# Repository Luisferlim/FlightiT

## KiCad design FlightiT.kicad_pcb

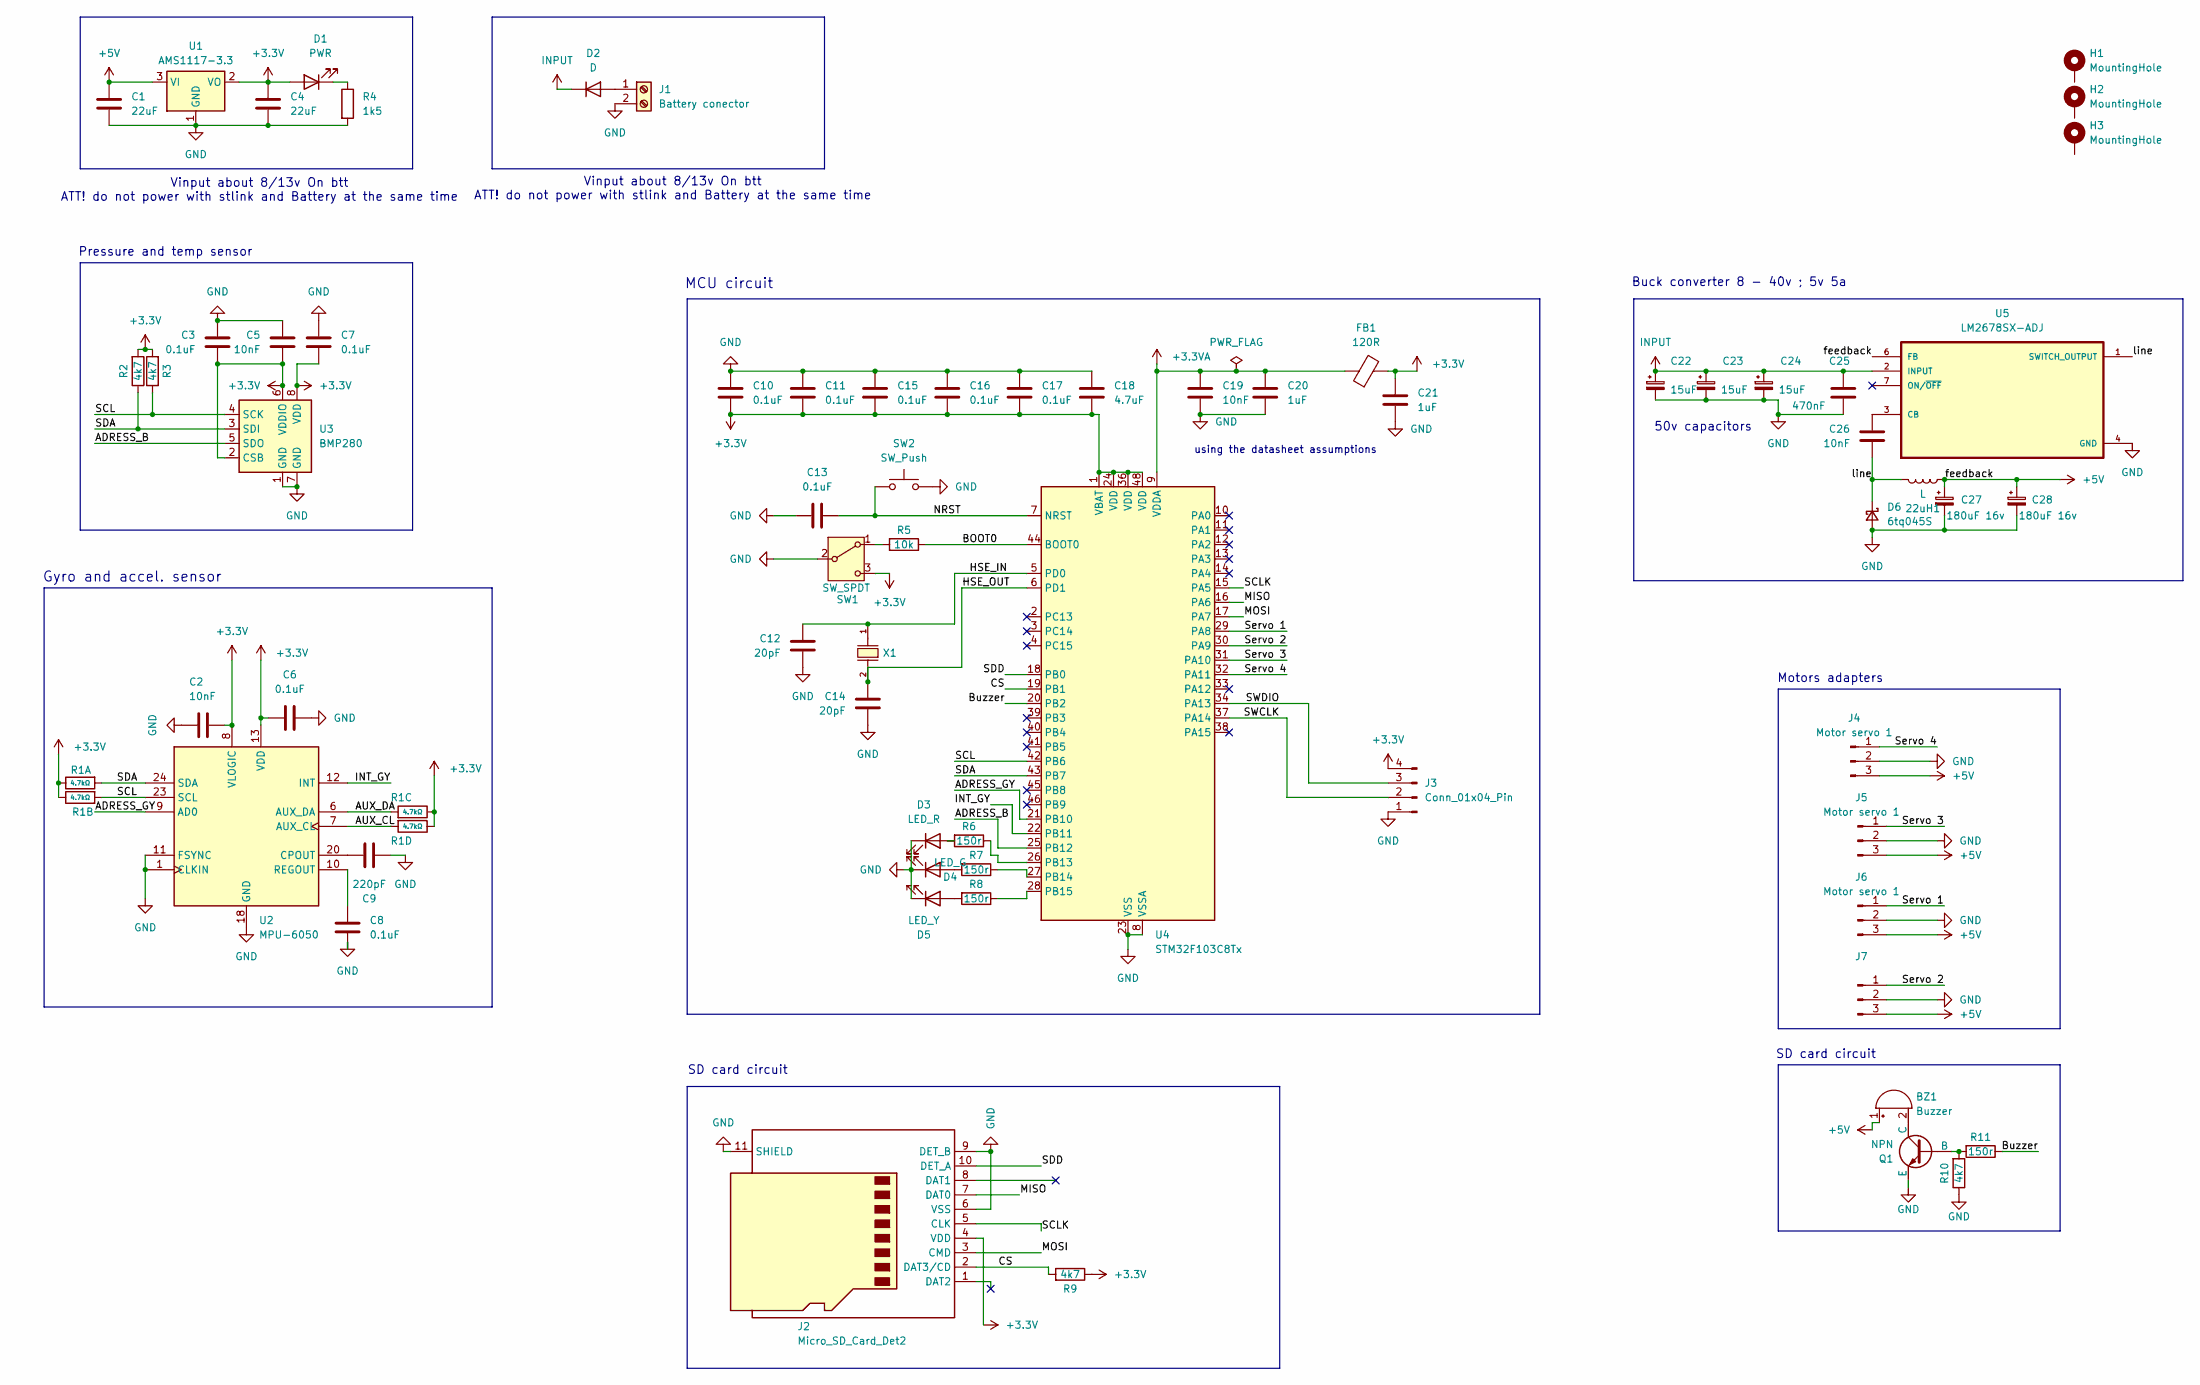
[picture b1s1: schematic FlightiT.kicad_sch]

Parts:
22uH1: L; L_Changjiang_FXL1040
BZ1: Buzzer; Buzzer_12x9.5RM7.6
C1, C4: 22uF; C_1206_3216Metric
C2, C5, C19, C26: 10nF; C_0805_2012Metric
C3, C6, C7, C8, C10, C11, C13, C15, C16, C17: 0.1uF; C_0402_1005Metric
C9: 220pF; C_0402_1005Metric
C12, C14: 20pF; C_0402_1005Metric
C18: 4.7uF; C_0805_2012Metric
C20, C21: 1uF; C_1206_3216Metric
C22, C23, C24: 15uF; CP_Radial_D5.0mm_P2.50mm
C25: 470nF; C_0402_1005Metric
C27, C28: 180uF 16v; CP_Radial_D5.0mm_P2.50mm
D1: PWR; LED_0603_1608Metric
D2: D; D_SOD-323
D3: LED_R; LED_0603_1608Metric
D4: LED_G; LED_0603_1608Metric
D5: LED_Y; LED_0603_1608Metric
D6: 6tq045S; TO-263-2_TabPin1
FB1: 120R; L_0603_1608Metric
H1, H2, H3: MountingHole; MountingHole_3.2mm_M3_ISO7380_Pad
J1: Battery conector; TerminalBlock_MaiXu_MX126-5.0-02P_1x02_P5.00mm
J2: Micro_SD_Card_Det2; microSD_HC_Molex_47219-2001
J3: Conn_01x04_Pin; PinHeader_1x04_P2.54mm_Horizontal
J4, J5, J6: Motor servo 1; PinHeader_1x03_P2.54mm_Vertical
J7: Motor servo 2; PinHeader_1x03_P2.54mm_Vertical
Q1: NPN; SOT-23
R1: 4.7kΩ; R_Array_Concave_4x0603; Tolerance ±5%; Part 4D03WGJ0472T5E; LCSC C1980
R2, R3, R9, R10: 4k7; R_0603_1608Metric
R4: 1k5; R_0603_1608Metric
R5: 10k; R_0603_1608Metric
R6, R7, R8, R11: 150r; R_0603_1608Metric
SW1: SW_SPDT; SW_SPDT_PCM12
SW2: SW_Push; SW_TS-1088-AR02016
U1: AMS1117-3.3; SOT-223-3_TabPin2
U2: MPU-6050; InvenSense_QFN-24_4x4mm_P0.5mm
U3: BMP280; Bosch_LGA-8_2x2.5mm_P0.65mm_ClockwisePinNumbering
U4: STM32F103C8Tx; LQFP-48_7x7mm_P0.5mm
U5: LM2678SX-ADJ; TO127P1435X464-8N
X1: X50328MSB2GI; Crystal_SMD_5032-2Pin_5.0x3.2mm; Frequency Tolerance ±10ppm; Part X50328MSB2GI; LCSC C115962

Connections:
+3.3V: C2.1, C3.2, C4.2, C5.2, C6.2, C7.2, C10.1, C11.1, C15.1, C16.1, C17.1, C18.1, C21.2, D1.2 (A), FB1.2, J2.4 (VDD), J3.4, R1.5, R1.6, R1.7, R1.8, R2.2, R3.2, R9.1, SW1.3 (C), U1.2 (VO), U2.8 (VLOGIC), U2.13 (VDD), U3.2 (CSB), U3.6 (VDDIO), U3.8 (VDD), U4.1 (VBAT), U4.24 (VDD), U4.36 (VDD), U4.48 (VDD); also elsewhere on the board
+3.3VA: C19.2, C20.2, FB1.1, U4.9 (VDDA)
+5V: 22uH1.1, BZ1.1 (+), C1.2, C27.1, C28.1, J4.3, J5.3, J6.3, J7.3, U1.3 (VI), U5.6 (FB); also elsewhere on the board
/ADRESS_B: U3.5 (SDO), U4.25 (PB12)
/ADRESS_GY: U2.9 (AD0), U4.21 (PB10)
/AUX_CL: R1.4, U2.7 (AUX_CL)
/AUX_DA: R1.3, U2.6 (AUX_DA)
/BOOT0: R5.1, U4.44 (BOOT0)
/Buzzer: R11.1, U4.20 (PB2)
/CS: J2.2 (DAT3/CD), R9.2, U4.19 (PB1)
/HSE_IN: C12.1, U4.5 (PD0), X1.1
/HSE_OUT: C14.2, U4.6 (PD1), X1.2
/INT_GY: U2.12 (INT), U4.22 (PB11)
/MISO: J2.7 (DAT0), U4.16 (PA6)
/MOSI: J2.3 (CMD), U4.17 (PA7)
/NRST: C13.1, SW2.1, U4.7 (NRST)
/SCL: R1.2, R3.1, U2.23 (SCL), U3.4 (SCK), U4.42 (PB6)
/SCLK: J2.5 (CLK), U4.15 (PA5)
/SDA: R1.1, R2.1, U2.24 (SDA), U3.3 (SDI), U4.43 (PB7); also elsewhere on the board
/SDD: J2.10 (DET_A), U4.18 (PB0)
/SWCLK: J3.2, U4.37 (PA14)
/SWDIO: J3.3, U4.34 (PA13)
/Servo 1: J6.1, U4.29 (PA8)
/Servo 2: J7.1, U4.30 (PA9)
/Servo 3: J5.1, U4.31 (PA10)
/Servo 4: J4.1, U4.32 (PA11)
/line: 22uH1.2, C26.1, D6.1 (K), U5.1 (SWITCH_OUTPUT); also elsewhere on the board
GND: C1.1, C2.2, C3.1, C4.1, C5.1, C6.1, C7.1, C8.1, C9.1, C10.2, C11.2, C12.2, C13.2, C14.1, C15.2, C16.2, C17.2, C18.2, C19.1, C20.1, C21.1, C22.2, C23.2, C24.2, C25.2, C27.2, C28.2, D3.1 (K), D4.1 (K), D5.1 (K), D6.2 (A), J1.2, J2.6 (VSS), J2.9 (DET_B), J2.11 (SHIELD), J3.1, J4.2, J5.2, J6.2, J7.2, Q1.3 (E), R4.2, R10.1, SW1.2 (B), SW2.2, U1.1 (GND), U2.1 (CLKIN), U2.11 (FSYNC), U2.18 (GND), U3.1 (GND), U3.7 (GND), U4.8 (VSSA), U4.23 (VSS), U4.35 (VSS), U4.47 (VSS), U5.4 (GND)
INPUT: C22.1, C23.1, C24.1, C25.1, D2.1 (K), U5.2 (INPUT)
unnamed: BZ1.2 (-), Q1.1 (C)
unnamed: D1.1 (K), R4.1
unnamed: D2.2 (A), J1.1
unnamed: D3.2 (A), R6.2
unnamed: D4.2 (A), R7.2
unnamed: D5.2 (A), R8.2
unnamed: Q1.2 (B), R10.2, R11.2
unnamed: R5.2, SW1.1 (A)
unnamed: C9.2, U2.20 (CPOUT)
unnamed: C8.2, U2.10 (REGOUT)
unnamed: R6.1, U4.26 (PB13)
unnamed: R7.1, U4.27 (PB14)
unnamed: R8.1, U4.28 (PB15)
unnamed: C26.2, U5.3 (CB)

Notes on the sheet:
Vinput about 8/13v On btt ATT! do not power with stlink and Battery at the same time
Buck converter 8 - 40v ; 5v 5a
Pressure and temp sensor
MCU circuit
50v capacitors
Motors adapters
SD card circuit
Gyro and accel. sensor
using the datasheet assumptions

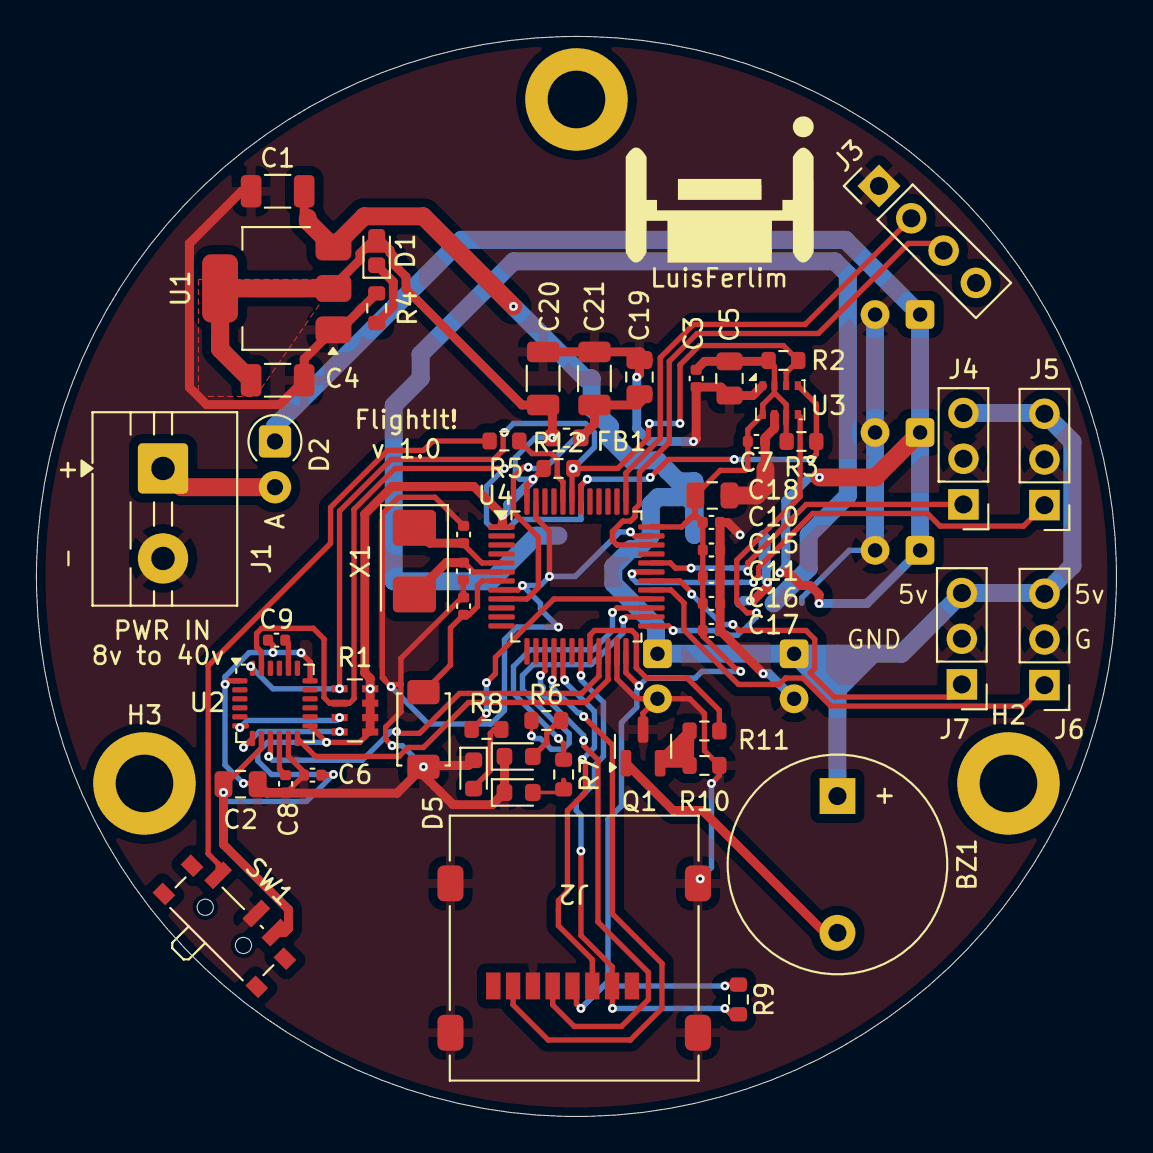
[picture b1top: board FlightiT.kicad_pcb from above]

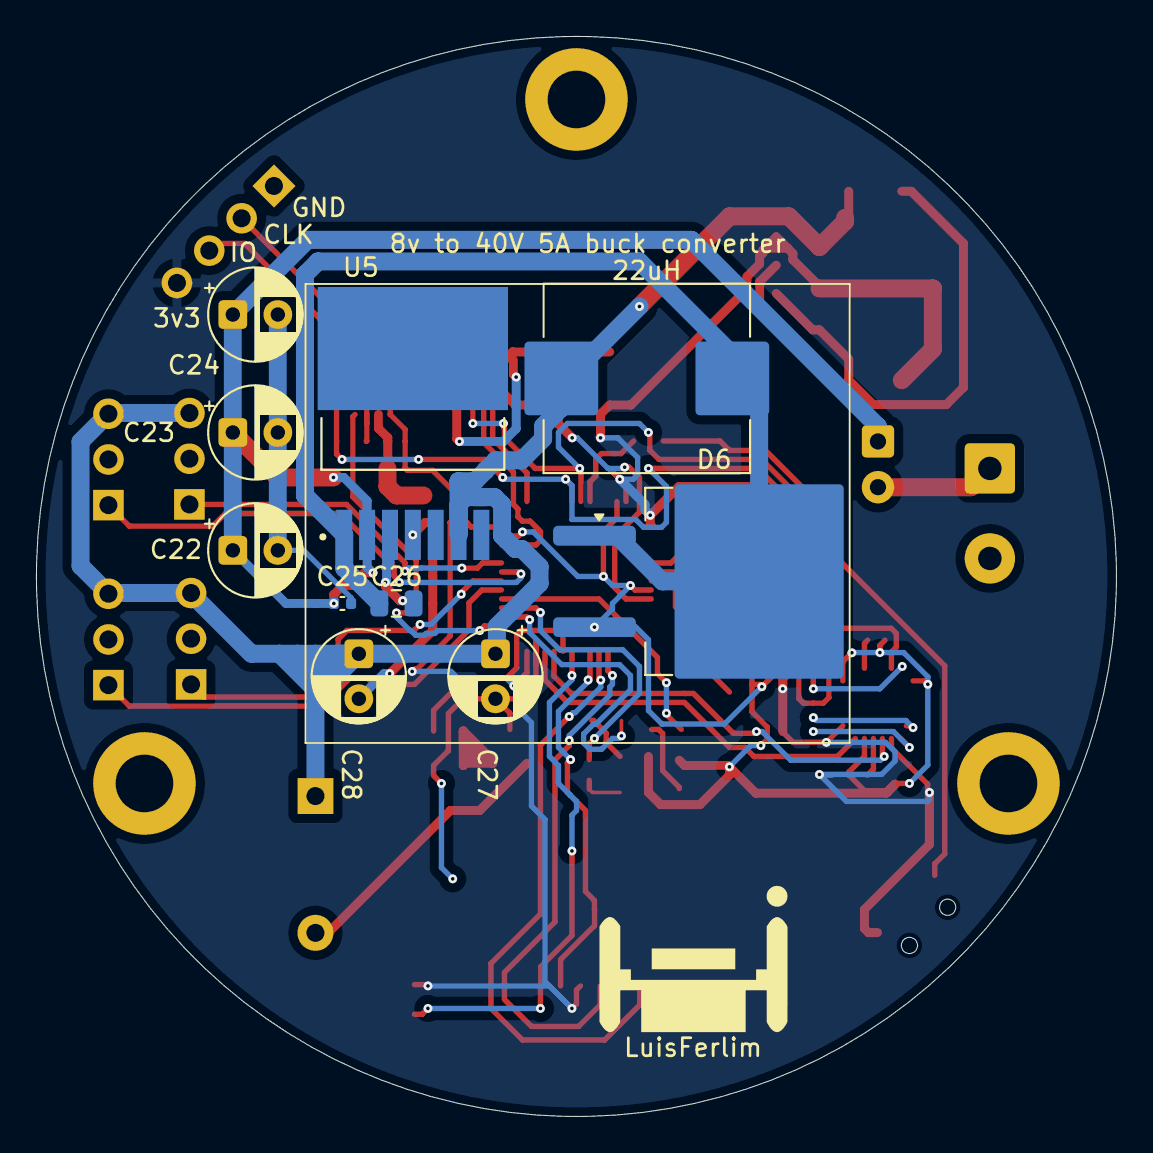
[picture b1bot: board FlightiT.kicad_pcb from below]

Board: 2 copper layers, 60.0 x 60.0 mm, 68 parts (10 on the bottom side), 42 nets.

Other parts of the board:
22uH: L; L_Changjiang_FXL1040
R12: 1k5; R_0603_1608Metric

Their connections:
+3.3V: R12.1; also elsewhere on the board
+5V: 22uH.1; also elsewhere on the board
/SDA: R12.2; also elsewhere on the board
/line: 22uH.2; also elsewhere on the board

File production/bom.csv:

Designator,Footprint,Quantity,Value,LCSC Part #
22UH,L_Changjiang_FXL1040,1,L,
BZ1,Buzzer_12x9.5RM7.6,1,Buzzer,
"C1, C4",1206,2,22uF,
"C10, C11, C13, C15, C16, C17, C3, C6, C7, C8",0402,10,0.1uF,
"C12, C14",0402,2,20pF,
C18,0805,1,4.7uF,
"C19, C2, C26, C5",0805,4,10nF,
"C20, C21",1206,2,1uF,
"C22, C23, C24",CP_Radial_D5.0mm_P2.50mm,3,15uF,
C25,0402,1,470nF,
"C27, C28",CP_Radial_D5.0mm_P2.50mm,2,180uF 16v,
C9,0402,1,220pF,
D1,0603,1,PWR,
D2,D_A-405_P2.54mm_Vertical_AnodeUp,1,D,
D3,0603,1,LED_R,
D4,0603,1,LED_G,
D5,0603,1,LED_Y,
D6,TO-263-2_TabPin1,1,6tq045S,
FB1,0603,1,120R,
J1,TerminalBlock_MaiXu_MX126-5.0-02P_1x02_P5.00mm,1,Battery conector,
J2,microSD_HC_Molex_47219-2001,1,Micro_SD_Card_Det2,
J3,PinHeader_1x04_P2.54mm_Vertical,1,Conn_01x04_Pin,
"J4, J5, J6",PinHeader_1x03_P2.54mm_Vertical,3,Motor servo 1,
J7,PinHeader_1x03_P2.54mm_Vertical,1,Motor servo 2,
Q1,SOT-23,1,NPN,
R1,R_Array_Concave_4x0603,1,4.7kΩ,C1980
"R10, R2, R3, R9",0603,4,4k7,
"R11, R6, R7, R8",0603,4,150r,
"R12, R4",0603,2,1k5,
R5,0603,1,10k,
SW1,SW_SPDT_PCM12,1,SW_SPDT,
SW2,SW_TS-1088-AR02016,1,SW_Push,
U1,SOT-223-3_TabPin2,1,AMS1117-3.3,
U2,InvenSense_QFN-24_4x4mm_P0.5mm,1,MPU-6050,
U3,Bosch_LGA-8_2x2.5mm_P0.65mm_ClockwisePinNumbering,1,BMP280,
U4,LQFP-48_7x7mm_P0.5mm,1,STM32F103C8Tx,
U5,TO127P1435X464-8N,1,LM2678SX-ADJ,
X1,Crystal_SMD_5032-2Pin_5.0x3.2mm,1,X50328MSB2GI,C115962

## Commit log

2025-09-06 routing init.
2025-09-07 solving issues from v1.0
